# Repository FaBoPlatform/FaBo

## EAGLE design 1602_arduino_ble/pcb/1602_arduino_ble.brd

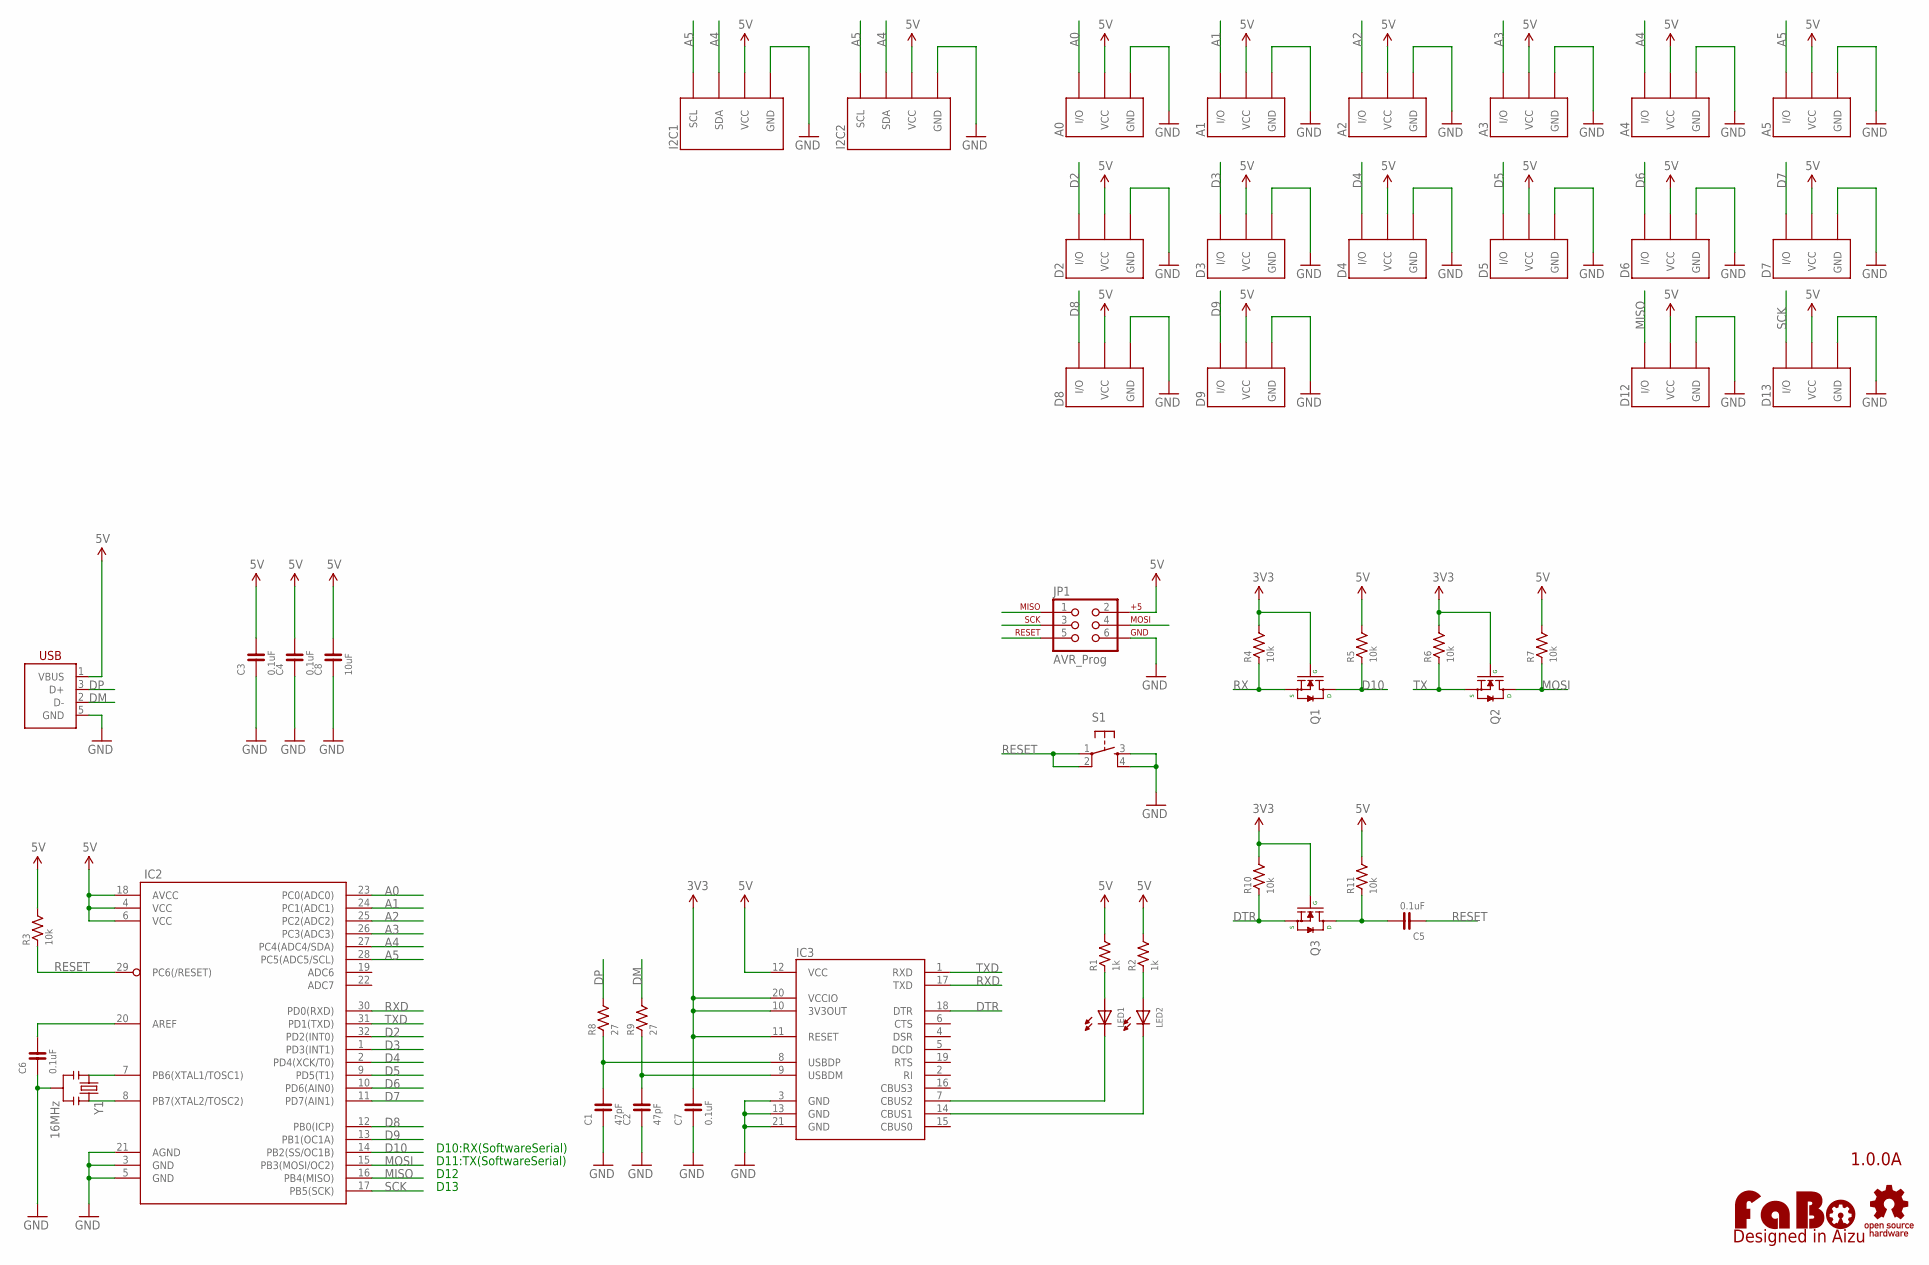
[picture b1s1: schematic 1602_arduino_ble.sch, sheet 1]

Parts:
A0, A1, A2, A3, A4, A5: FABO_BRICK_3PIN-S03B-PASK-2; FABO_BRICK_3PIN_S03B-PASK-2
C1, C2: 47pF; 0603
C3, C4, C5, C6, C7: 0.1uF; 0603
C8: 10uF; 0603
D2, D3, D4, D5, D6, D7, D8, D9, D12, D13: FABO_BRICK_3PIN-B03B-PASK-1; FABO_BRICK_3PIN_B03B-PASK-1
I2C1, I2C2: FABO_BRICK_I2C-S04B-PASK-2; FABO_BRICK_I2C_S04B-PASK-2
IC2: ATMEGA328P-AU-TQFP32; TQFP-32-08
IC3: FT231XQ; QFN-20
JP1: AVR_Prog; TC2030-MCP
LED1, LED2: LED-0603; 0603
Q1, Q2, Q3: MOSFET-N-BSS138; SOT23-3
R1, R2: 1k; 0603
R3, R4, R5, R6, R7, R10, R11: 10k; 0603
R8, R9: 27; 0603
S1: TACT-SWITCH-SMD_KMR2; KMR2
U$2: LOGO_OSHW-M; LOGO_OSHW_M
U$3: LOGO_FABO-M; LOGO_FABO_MS
USB2: USB-MICRO_B_SMT; DX4R005JJ2R1800
Y1: 16MHz; RESONATOR_SMD

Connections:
3V3: C7.2, IC3.10 (3V3OUT), IC3.11 (RESET), IC3.20 (VCCIO), Q1.1 (G), Q2.1 (G), Q3.1 (G), R4.2, R6.2, R10.2; also elsewhere on the board
5V: A0.VCC, A1.VCC, A2.VCC, A3.VCC, A4.VCC, A5.VCC, C3.2, C4.2, C8.2, D2.VCC, D3.VCC, D4.VCC, D5.VCC, D6.VCC, D7.VCC, D8.VCC, D9.VCC, D12.VCC, D13.VCC, I2C1.VCC, I2C2.VCC, IC2.4 (VCC), IC2.6 (VCC), IC2.18 (AVCC), IC3.12 (VCC), JP1.2, R1.2, R2.2, R3.2, R5.2, R7.2, R11.2, USB2.1 (VBUS)
A0: A0.I/O, IC2.23 (PC0(ADC0))
A1: A1.I/O, IC2.24 (PC1(ADC1))
A2: A2.I/O, IC2.25 (PC2(ADC2))
A3: A3.I/O, IC2.26 (PC3(ADC3))
A4: A4.I/O, I2C1.SDA, I2C2.SDA, IC2.27 (PC4(ADC4/SDA))
A5: A5.I/O, I2C1.SCL, I2C2.SCL, IC2.28 (PC5(ADC5/SCL))
D2: D2.I/O, IC2.32 (PD2(INT0))
D3: D3.I/O, IC2.1 (PD3(INT1))
D4: D4.I/O, IC2.2 (PD4(XCK/T0))
D5: D5.I/O, IC2.9 (PD5(T1))
D6: D6.I/O, IC2.10 (PD6(AIN0))
D7: D7.I/O, IC2.11 (PD7(AIN1))
D8: D8.I/O, IC2.12 (PB0(ICP))
D9: D9.I/O, IC2.13 (PB1(OC1A))
D10: IC2.14 (PB2(SS/OC1B)), Q1.3 (D), R5.1; also elsewhere on the board
DM: R9.2, USB2.2 (D-)
DP: R8.2, USB2.3 (D+)
DTR: IC3.18 (DTR), Q3.2 (S), R10.1
GND: A0.GND, A1.GND, A2.GND, A3.GND, A4.GND, A5.GND, C1.1, C2.1, C3.1, C4.1, C6.1, C7.1, C8.1, D2.GND, D3.GND, D4.GND, D5.GND, D6.GND, D7.GND, D8.GND, D9.GND, D12.GND, D13.GND, I2C1.GND, I2C2.GND, IC2.3 (GND), IC2.5 (GND), IC2.21 (AGND), IC3.3 (GND), IC3.13 (GND), IC3.21 (GND), JP1.6, S1.3, S1.4, USB2.5 (GND), Y1.2; also elsewhere on the board
MISO: D12.I/O, IC2.16 (PB4(MISO)), JP1.1
MOSI: IC2.15 (PB3(MOSI/OC2)), JP1.4, Q2.3 (D), R7.1; also elsewhere on the board
unnamed: LED1.ANODE, R1.1
unnamed: C6.2, IC2.20 (AREF)
unnamed: IC2.8 (PB7(XTAL2/TOSC2)), Y1.3
unnamed: IC2.7 (PB6(XTAL1/TOSC1)), Y1.1
unnamed: C1.2, IC3.8 (USBDP), R8.1
unnamed: C2.2, IC3.9 (USBDM), R9.1
unnamed: IC3.14 (CBUS1), LED2.CATHODE
unnamed: IC3.7 (CBUS2), LED1.CATHODE
unnamed: C5.2, Q3.3 (D), R11.1
unnamed: LED2.ANODE, R2.1
RESET: C5.1, IC2.29 (PC6(/RESET)), JP1.5, R3.1, S1.1, S1.2
RX: Q1.2 (S), R4.1
RXD: IC2.30 (PD0(RXD)), IC3.17 (TXD)
SCK: D13.I/O, IC2.17 (PB5(SCK)), JP1.3
TX: Q2.2 (S), R6.1
TXD: IC2.31 (PD1(TXD)), IC3.1 (RXD)

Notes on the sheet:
1.0.0A
D11:TX(SoftwareSerial)
D12
D13
D10:RX(SoftwareSerial)

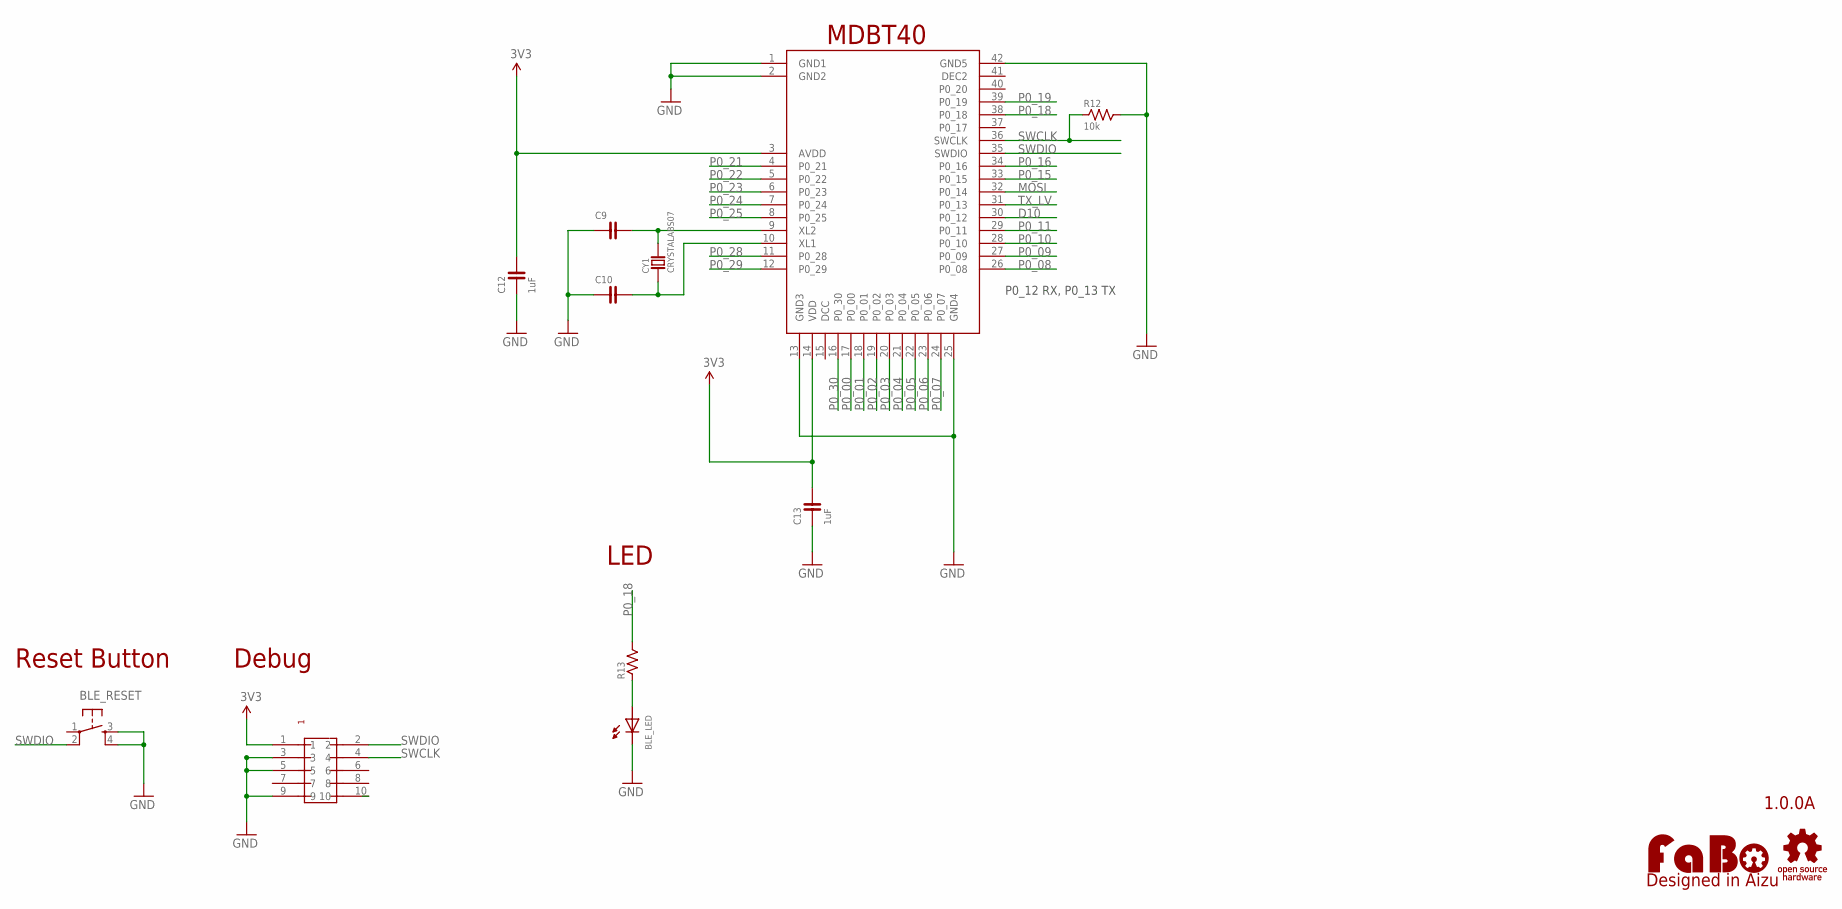
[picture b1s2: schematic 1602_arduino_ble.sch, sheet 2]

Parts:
BLE_LED: LED-0603; 0603
BLE_RESET: TACT-SWITCH-SMD_KMR2; KMR2
C9, C10: CAPACITOR-0603_NARROW; 0603-NARROW
C12, C13: 1uF; 0603-NARROW
CY1: CRYSTALABS07; ABRACOM-ABS07-32.768KHZ
R12: 10k; 0603-NARROW
R13: RESISTOR-0603-NARROW; 0603-NARROW
U$7: RAYTAC-MDBT40
U$8: PIN-HEADER-SMT(1.27MM)2X5

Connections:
3V3: C12.2, C13.2, U$7.3 (AVDD), U$7.14 (VDD), U$8.1; also elsewhere on the board
D10: U$7.30 (P0_12); also elsewhere on the board
GND: BLE_LED.CATHODE, BLE_RESET.3, BLE_RESET.4, C9.1, C10.1, C12.1, C13.1, R12.2, U$7.1 (GND1), U$7.2 (GND2), U$7.13 (GND3), U$7.25 (GND4), U$7.42 (GND5), U$8.3, U$8.5, U$8.9; also elsewhere on the board
MOSI: U$7.32 (P0_14); also elsewhere on the board
unnamed: C9.2, CY1.P$2, U$7.9 (XL2)
unnamed: C10.2, CY1.P$1, U$7.10 (XL1)
unnamed: BLE_LED.ANODE, R13.1
P0_00: U$7.17 (P0_00)
P0_01: U$7.18 (P0_01)
P0_02: U$7.19 (P0_02)
P0_03: U$7.20 (P0_03)
P0_04: U$7.21 (P0_04)
P0_05: U$7.22 (P0_05)
P0_06: U$7.23 (P0_06)
P0_07: U$7.24 (P0_07)
P0_08: U$7.26 (P0_08)
P0_09: U$7.27 (P0_09)
P0_10: U$7.28 (P0_10)
P0_11: U$7.29 (P0_11)
P0_15: U$7.33 (P0_15)
P0_16: U$7.34 (P0_16)
P0_18: R13.2, U$7.38 (P0_18)
P0_19: U$7.39 (P0_19)
P0_21: U$7.4 (P0_21)
P0_22: U$7.5 (P0_22)
P0_23: U$7.6 (P0_23)
P0_24: U$7.7 (P0_24)
P0_25: U$7.8 (P0_25)
P0_28: U$7.11 (P0_28)
P0_29: U$7.12 (P0_29)
P0_30: U$7.16 (P0_30)
RESET1: U$8.10
SWCLK: R12.1, U$7.36 (SWCLK), U$8.4
SWDIO: BLE_RESET.2, U$7.35 (SWDIO), U$8.2
TX_LV: U$7.31 (P0_13)

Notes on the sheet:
1.0.0A
Reset Button
MDBT40
LED
Debug
P0_12 RX, P0_13 TX

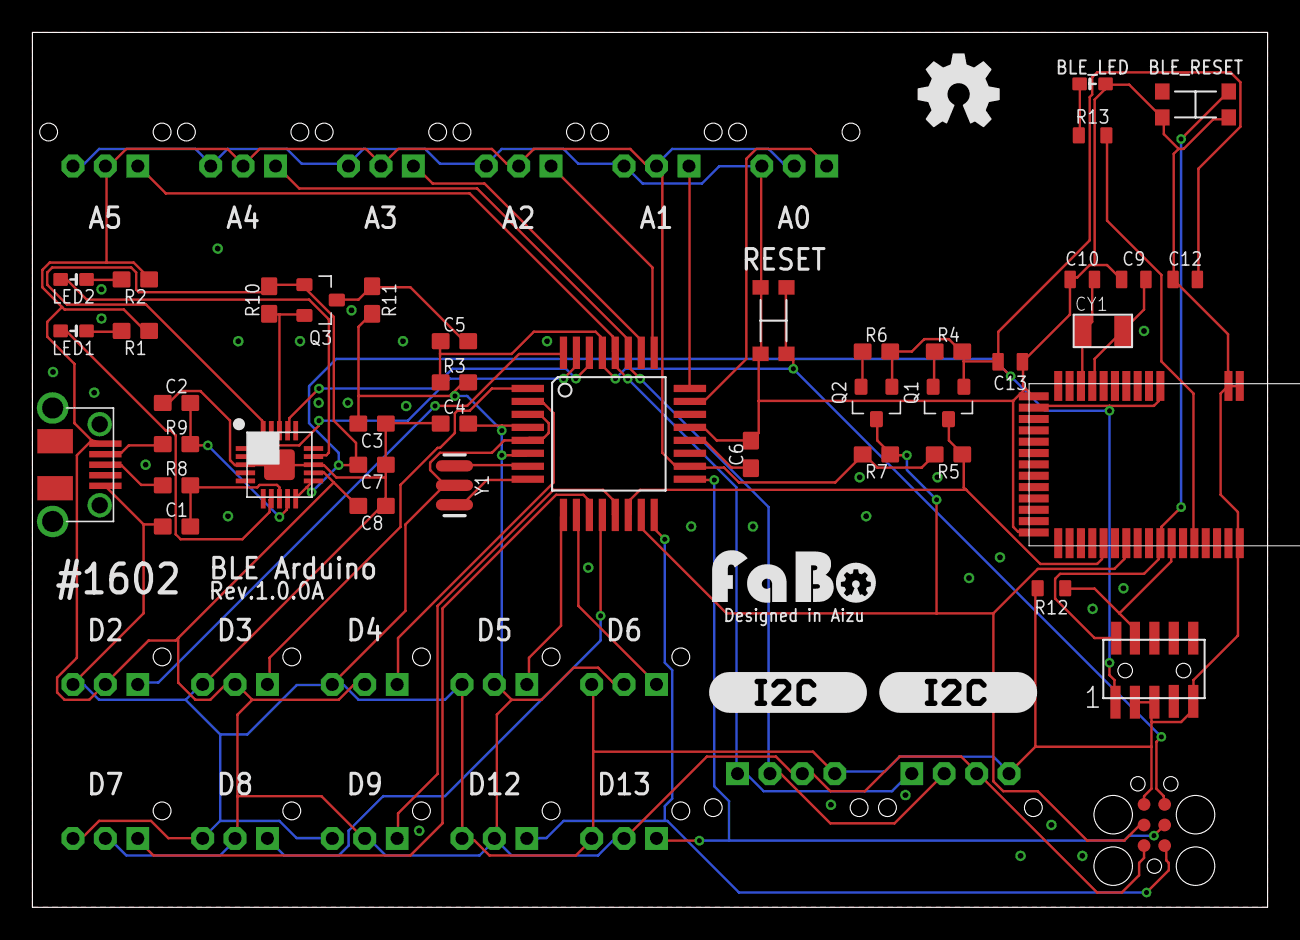
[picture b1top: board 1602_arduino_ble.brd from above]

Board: 2 copper layers, 76.2 x 54.0 mm, 63 parts (0 on the bottom side), 45 nets.

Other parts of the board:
U$4, U$6: LOGO_SILK_I2C

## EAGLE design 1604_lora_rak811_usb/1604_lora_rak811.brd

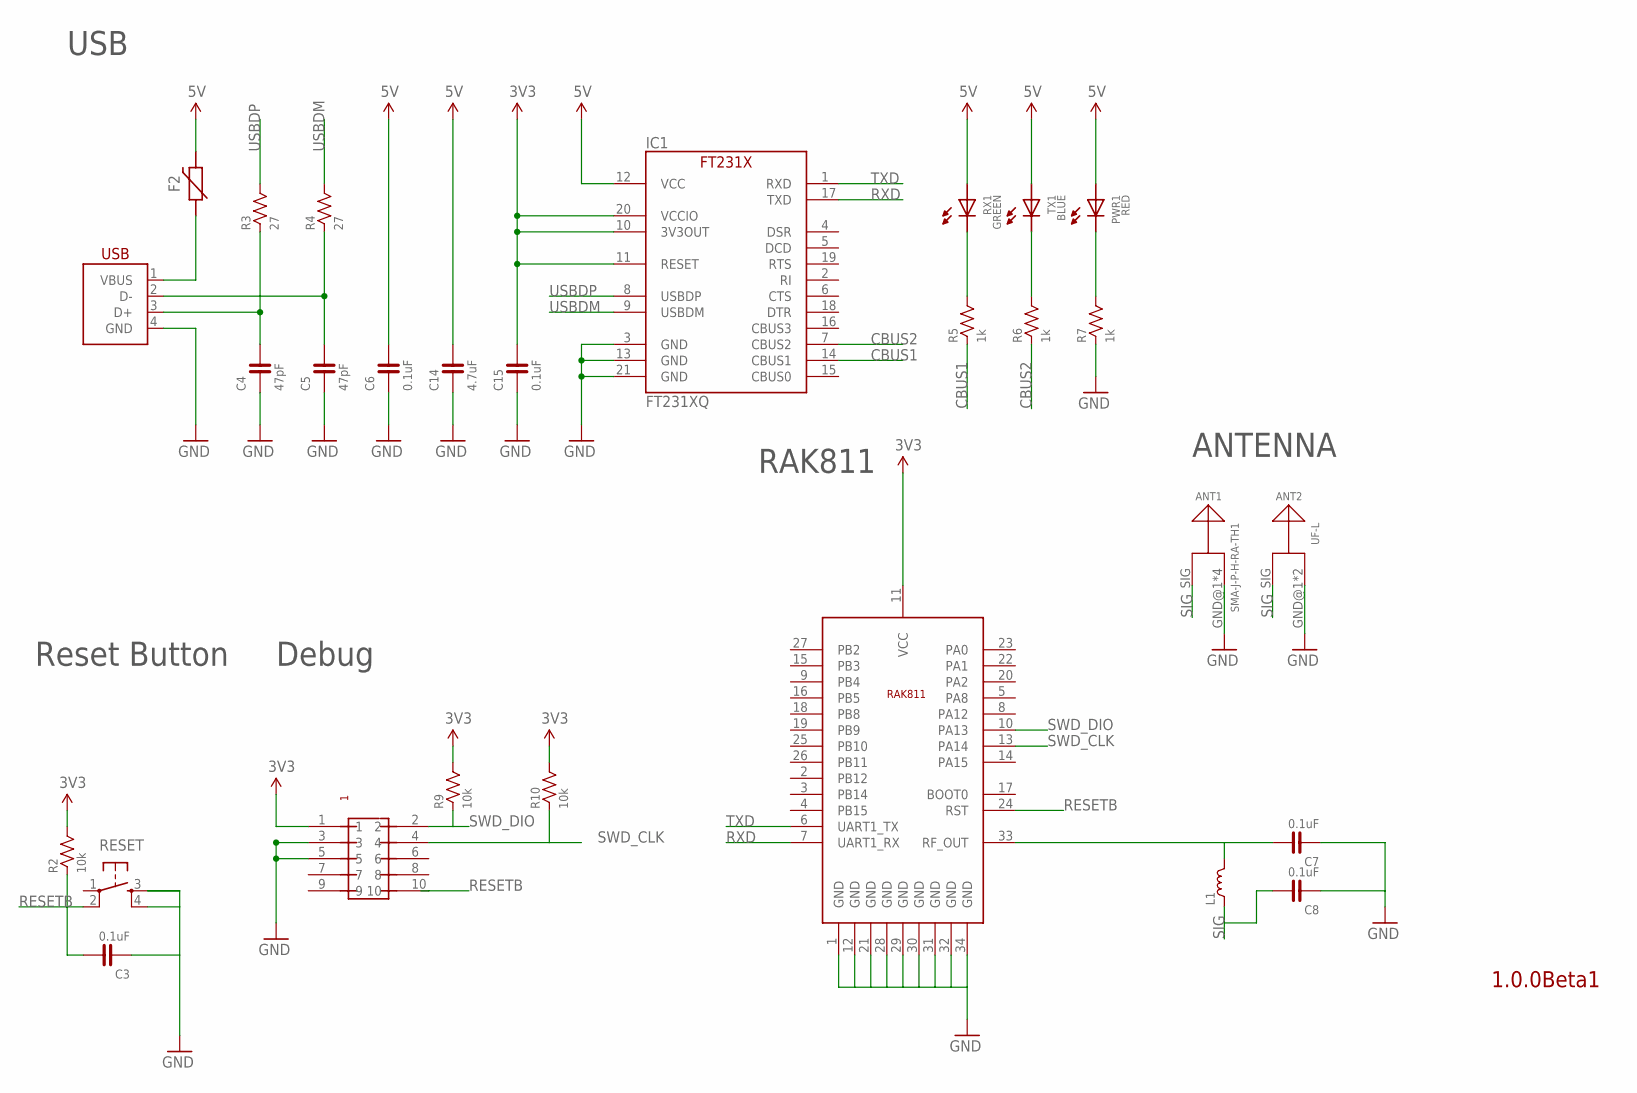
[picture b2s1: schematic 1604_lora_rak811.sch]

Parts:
ANT1: SMA-J-P-H-RA-TH1; SMA–J–P–H–RA–TH1
ANT2: UF-L; HIROSE-UF-L
C3, C6, C7, C8, C15: 0.1uF; 0603-NARROW
C4, C5: 47pF; 0603-NARROW
C14: 4.7uF; 0603-NARROW
F2: POLYSWITCH; NANOSMDC035F
IC1: FT231XQ; QFN-20_FT231X
L1: COIL-0603; 0603
PWR1: RED; 0603-NARROW
R2, R9, R10: 10k; 0603-NARROW
R3, R4: 27; 0603-NARROW
R5, R6, R7: 1k; 0603-NARROW
RESET: TACT-SWITCH-SMD_KMR2; KMR2
RX1: GREEN; 0603-NARROW
TX1: BLUE; 0603-NARROW
U$2: RAK811
U$8: PIN-HEADER-SMT(1.27MM)2X5
USB1: USB-B_PTH; USB-4AF103BS

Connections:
3V3: C15.2, IC1.10 (3V3OUT), IC1.11 (RESET), IC1.20 (VCCIO), R2.2, R9.2, R10.2, U$2.11 (VCC), U$8.1
5V: C6.2, C14.2, F2.2, IC1.12 (VCC), PWR1.ANODE, RX1.ANODE, TX1.ANODE
CBUS1: IC1.14 (CBUS1), R5.1
CBUS2: IC1.7 (CBUS2), R6.1
GND: ANT1.GND@1 (GND), ANT1.GND@2 (GND), ANT1.GND@3 (GND), ANT1.GND@4 (GND), ANT2.GND@1 (GND), ANT2.GND@2 (GND), C3.1, C4.1, C5.1, C6.1, C7.1, C8.1, C14.1, C15.1, IC1.3 (GND), IC1.13 (GND), IC1.21 (GND), R7.1, RESET.3, RESET.4, U$2.1 (GND), U$2.12 (GND), U$2.21 (GND), U$2.28 (GND), U$2.29 (GND), U$2.30 (GND), U$2.31 (GND), U$2.32 (GND), U$2.34 (GND), U$8.3, U$8.5, USB1.4 (GND)
unnamed: C7.2, L1.2, U$2.33 (RF_OUT)
unnamed: C5.2, R4.1, USB1.2 (D-)
unnamed: C4.2, R3.1, USB1.3 (D+)
unnamed: R5.2, RX1.CATHODE
unnamed: R6.2, TX1.CATHODE
unnamed: PWR1.CATHODE, R7.2
RESETB: C3.2, R2.1, RESET.2, U$2.24 (RST), U$8.10
RXD: IC1.17 (TXD), U$2.7 (UART1_RX)
SIG: ANT1.SIG, ANT2.SIG, C8.2, L1.1
SWD_CLK: R10.1, U$2.13 (PA14), U$8.4
SWD_DIO: R9.1, U$2.10 (PA13), U$8.2
TXD: IC1.1 (RXD), U$2.6 (UART1_TX)
USBDM: IC1.9 (USBDM), R4.2
USBDP: IC1.8 (USBDP), R3.2
VBUS1: F2.1, USB1.1 (VBUS)

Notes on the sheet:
1.0.0Beta1
Reset Button
Debug
RAK811
USB
ANTENNA

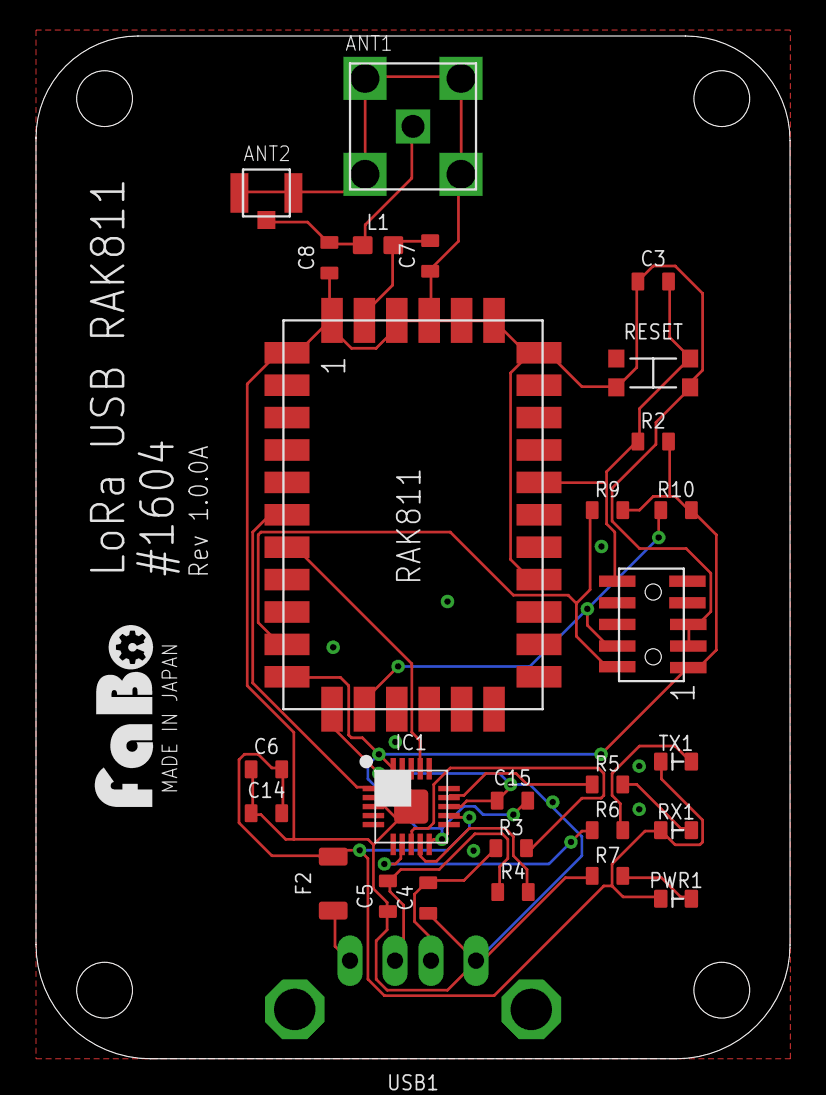
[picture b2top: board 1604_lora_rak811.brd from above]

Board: 2 copper layers, 41.9 x 56.8 mm, 29 parts (0 on the bottom side), 20 nets.

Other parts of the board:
U$3: LOGO_FABO_MS

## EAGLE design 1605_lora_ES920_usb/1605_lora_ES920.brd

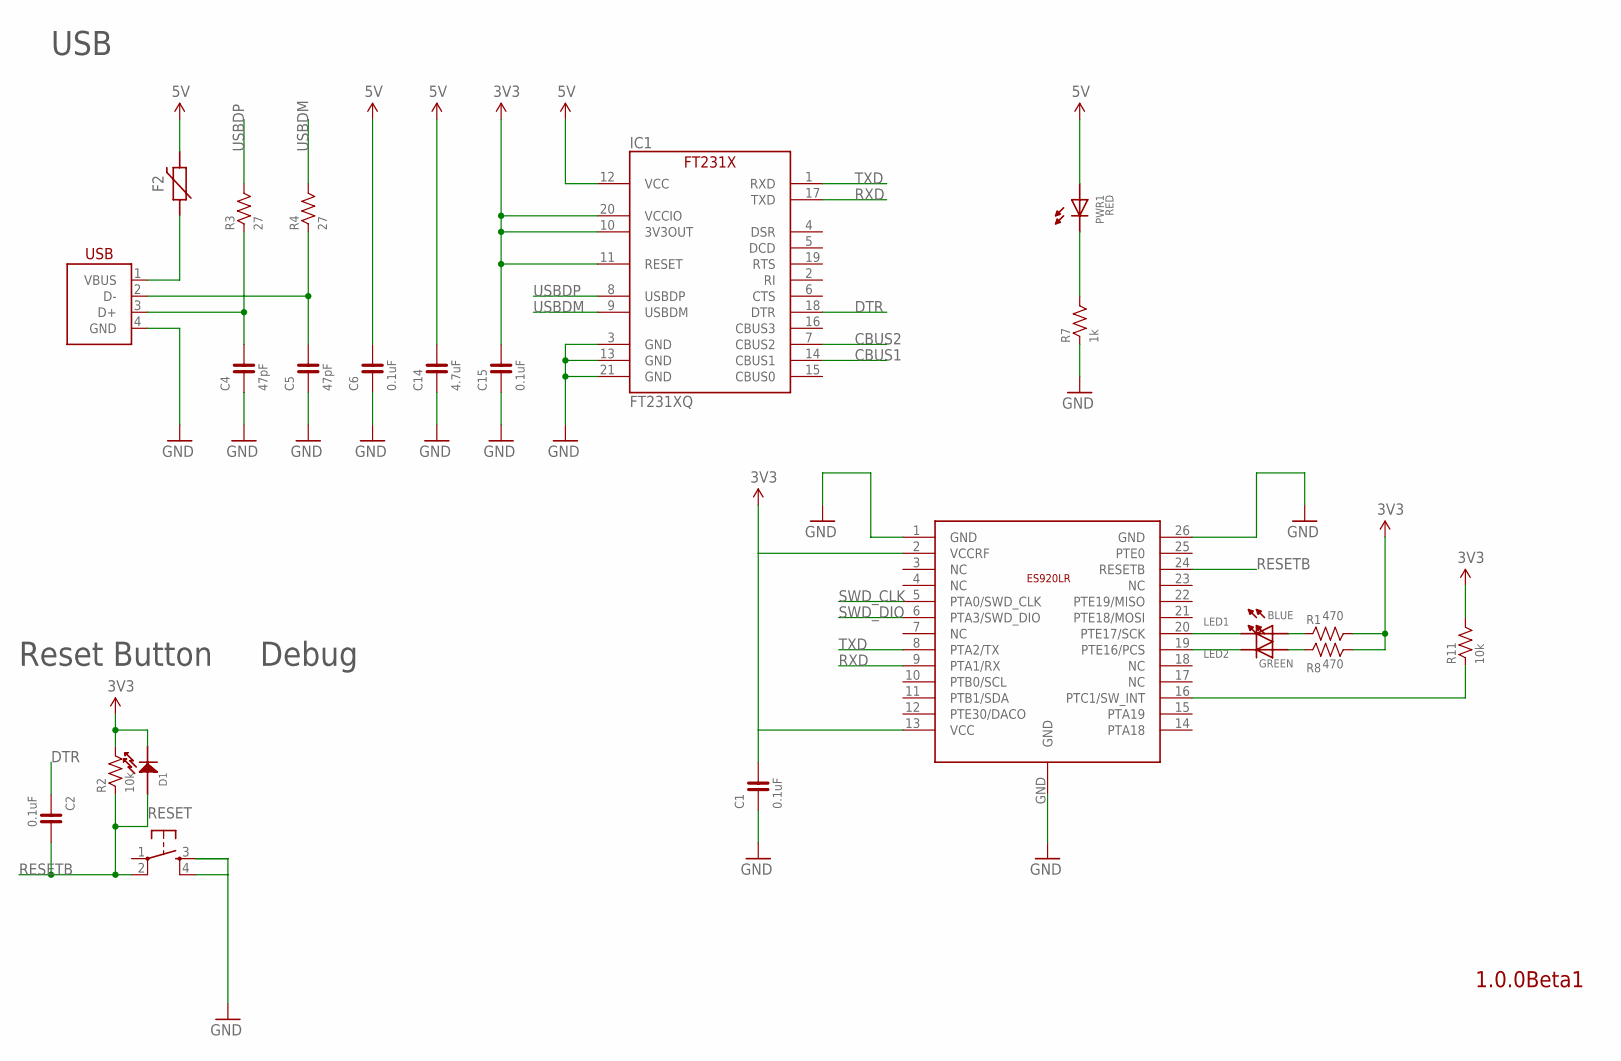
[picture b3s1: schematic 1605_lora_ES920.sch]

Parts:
C1, C2, C6, C15: 0.1uF; 0603-NARROW
C4, C5: 47pF; 0603-NARROW
C14: 4.7uF; 0603-NARROW
D1: DIODE0603; 0603
F2: POLYSWITCH; NANOSMDC035F
IC1: FT231XQ; QFN-20_FT231X
LED1: BLUE; 0603
LED2: GREEN; 0603
PWR1: RED; 0603-NARROW
R1, R8: 470; 0603-NARROW
R2, R11: 10k; 0603-NARROW
R3, R4: 27; 0603-NARROW
R7: 1k; 0603-NARROW
RESET: TACT-SWITCH-SMD_KMR2; KMR2
U$4: ES920LR
USB1: USB-B_PTH; USB-4AF103BS

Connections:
3V3: C1.2, C15.2, D1.CATHODE, IC1.10 (3V3OUT), IC1.11 (RESET), IC1.20 (VCCIO), R1.2, R2.2, R8.2, R11.2, U$4.2 (VCCRF), U$4.13 (VCC)
5V: C6.2, C14.2, F2.2, IC1.12 (VCC), PWR1.ANODE
CBUS1: IC1.14 (CBUS1)
CBUS2: IC1.7 (CBUS2)
DTR: C2.1, IC1.18 (DTR)
GND: C1.1, C4.1, C5.1, C6.1, C14.1, C15.1, IC1.3 (GND), IC1.13 (GND), IC1.21 (GND), R7.1, RESET.3, RESET.4, U$4.1 (GND), U$4.26 (GND), U$4.GND, USB1.4 (GND)
unnamed: LED2.CATHODE, U$4.19 (PTE16/PCS)
unnamed: LED1.CATHODE, U$4.20 (PTE17/SCK)
unnamed: LED1.ANODE, R1.1
unnamed: LED2.ANODE, R8.1
unnamed: C5.2, R4.1, USB1.2 (D-)
unnamed: C4.2, R3.1, USB1.3 (D+)
unnamed: PWR1.CATHODE, R7.2
unnamed: R11.1, U$4.16 (PTC1/SW_INT)
RESETB: C2.2, D1.ANODE, R2.1, RESET.2, U$4.24 (RESETB)
RXD: IC1.17 (TXD), U$4.9 (PTA1/RX)
SWD_CLK: U$4.5 (PTA0/SWD_CLK)
SWD_DIO: U$4.6 (PTA3/SWD_DIO)
TXD: IC1.1 (RXD), U$4.8 (PTA2/TX)
USBDM: IC1.9 (USBDM), R4.2
USBDP: IC1.8 (USBDP), R3.2
VBUS1: F2.1, USB1.1 (VBUS)

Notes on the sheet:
1.0.0Beta1
Reset Button
Debug
USB

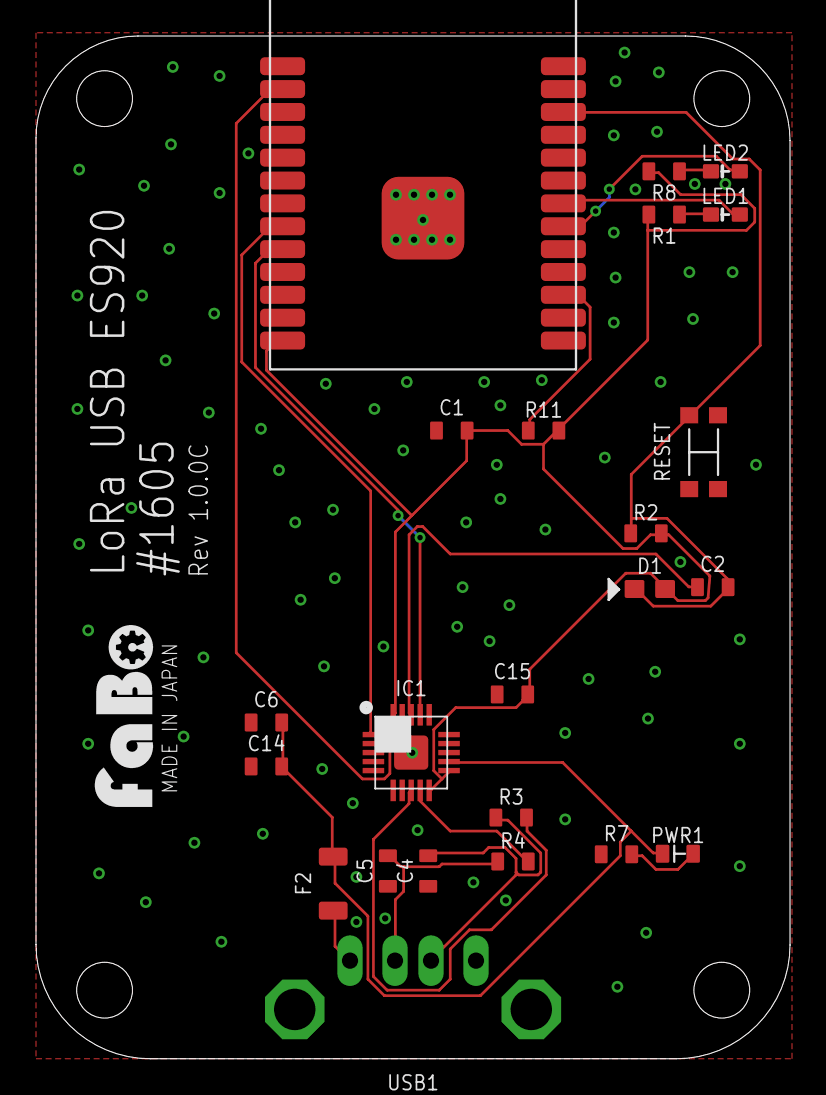
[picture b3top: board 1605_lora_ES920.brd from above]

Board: 2 copper layers, 41.9 x 56.8 mm, 24 parts (0 on the bottom side), 18 nets.

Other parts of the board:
U$3: LOGO_FABO_MS

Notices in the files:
parts and their libraries:
FaBo-Capacitor: Released under the Creative Commons Attribution-ShareAlike 4.0 License
https://creativecommons.org/licenses/by-sa/4.0
FaBo-etc: Released under the Creative Commons
